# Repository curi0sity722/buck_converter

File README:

## Hardware Design

### Buck Converter

### PCB Layout

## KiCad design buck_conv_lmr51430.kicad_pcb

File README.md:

This repository contains the design and development of a buck (step-down) DC-DC converter, focused on evaluating different controller ICs and design approaches to achieve the same functional goal.

## Hardware Design

### Buck Converter

### PCB Layout

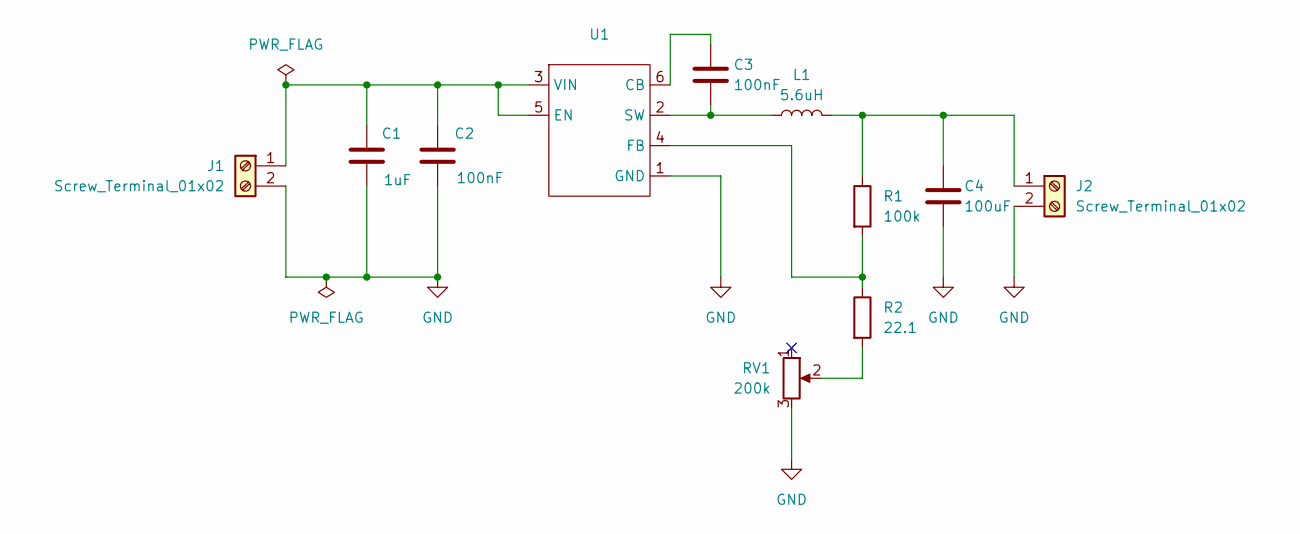
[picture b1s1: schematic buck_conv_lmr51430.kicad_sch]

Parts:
C1: 1uF; C_0805_2012Metric
C2: 100nF; C_0805_2012Metric
C3: 100nF; C_0603_1608Metric
C4: 100uF; CP_Radial_D6.3mm_P2.50mm
J1, J2: Screw_Terminal_01x02; TerminalBlock_Phoenix_MKDS-1,5-2_1x02_P5.00mm_Horizontal
L1: 5.6uH; L_APV_APH1030
R1: 100k; R_Axial_DIN0204_L3.6mm_D1.6mm_P5.08mm_Horizontal
R2: 22.1; R_Axial_DIN0204_L3.6mm_D1.6mm_P5.08mm_Horizontal
RV1: 200k; Potentiometer_Bourns_3266Y_Vertical
U1: SOT-23-6

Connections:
GND: C1.2, C2.2, C4.2, J1.2, J2.2, RV1.3, U1.1 (GND)
unnamed: C1.1, C2.1, J1.1, U1.3 (VIN), U1.5 (EN)
unnamed: C4.1, J2.1, L1.2, R1.1
unnamed: R2.2, RV1.2
unnamed: C3.1, U1.6 (CB)
unnamed: R1.2, R2.1, U1.4 (FB)
unnamed: C3.2, L1.1, U1.2 (SW)

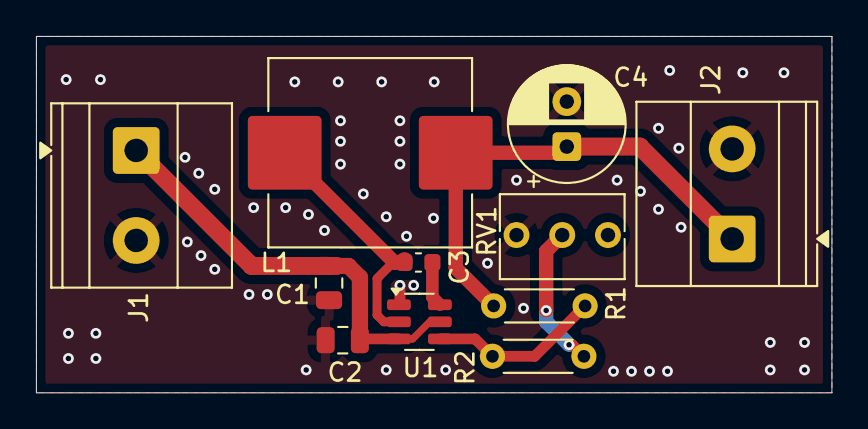
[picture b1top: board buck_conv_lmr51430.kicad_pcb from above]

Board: 2 copper layers, 44.2 x 19.8 mm, 11 parts (0 on the bottom side), 7 nets.

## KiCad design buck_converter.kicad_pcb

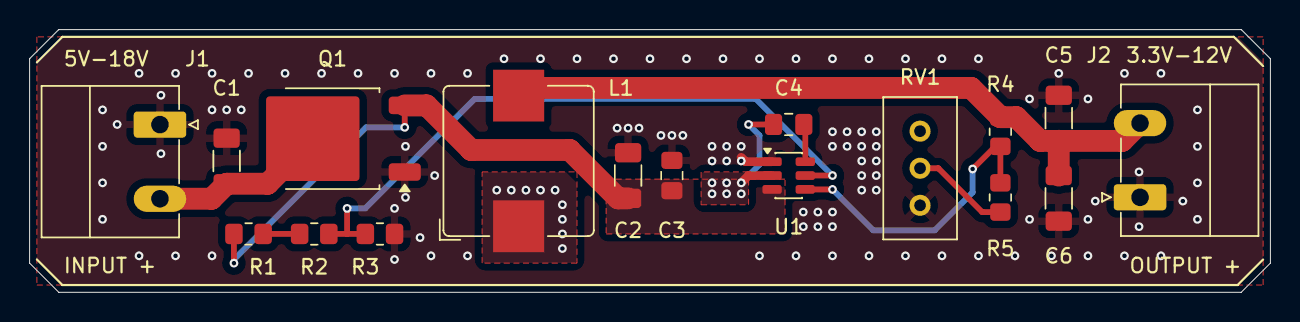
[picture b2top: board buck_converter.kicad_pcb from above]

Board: 2 copper layers, 85.0 x 18.0 mm, 17 parts (0 on the bottom side), 10 nets.

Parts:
C1, C2, C5, C6: 22u; C_1206_3216Metric_Pad1.33x1.80mm_HandSolder
C3, C4: 100n; C_0805_2012Metric_Pad1.18x1.45mm_HandSolder
J1: Input Screw Terminal; PhoenixContact_MC_1,5_2-G-5.08_1x02_P5.08mm_Horizontal
J2: Output Screw Terminal; PhoenixContact_MC_1,5_2-G-5.08_1x02_P5.08mm_Horizontal
L1: 15u; L_Bourns_SRP1038C_10.0x10.0mm
Q1: SUD09P10-195; TO-252-2
R1, R2, R3, R4: 100K; R_0805_2012Metric_Pad1.20x1.40mm_HandSolder
R5: 5K; R_0805_2012Metric_Pad1.20x1.40mm_HandSolder
RV1: 20K; Potentiometer_Bourns_3296W_Vertical
U1: TPS54308; SOT-23-6

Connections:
/EN: R2.2, R3.1, U1.5 (EN)
/FB: R4.2, R5.1, U1.4 (FB)
/SW: C4.2, L1.1, U1.2 (SW)
/VIN: C1.1, J1.2, Q1.2 (D)
/VIN_P: C2.1, C3.1, Q1.3 (S), R1.1, U1.3 (VIN)
/VOUT: C5.1, C6.1, J2.2, L1.2, R4.1
GND: C1.2, C2.2, C3.2, C5.2, C6.2, J1.1, J2.1, Q1.1 (G), R3.2, RV1.3, U1.1 (GND)
unnamed: R1.2, R2.1
unnamed: R5.2, RV1.2
unnamed: C4.1, U1.6 (BOOT)

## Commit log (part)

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2025-12-19 first push
2025-12-20 Fixed
2025-12-24 Add PCB v2 design with LMR51430
2025-12-24 README for the project
2025-12-24 Add variable output feedback network
2025-12-24 Inductor selection and footprint fix
2026-01-19 changes regarding the inductor
2026-01-19 rajath final touches
